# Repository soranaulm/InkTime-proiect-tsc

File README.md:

# InkTime - Open Source Smartwatch

InkTime este un smartwatch open source și accesibil, bazat pe un display e-paper și microcontroller-ul nRF52840.

## Diagramă bloc

```
┌─────────────┐     ┌─────────────────────────────────────────────────┐
│  USB-C      │─5V─▶│                                                 │
└─────────────┘     │                                                 │
                    │  BQ25180YBGR (LiPo Charger)                    │
┌─────────────┐     │         │ VBAT                                  │
│ AKYGA       │────▶│         ▼                                       │
│ LP502030    │     │  RT6160AWSC (DC/DC) ──▶ 3.3V                   │
│ 3.7V 250mAh │     └─────────────────────────────────────────────────┘
└─────────────┘                    │ 3V3
                                   ▼
                    ┌──────────────────────────────┐
                    │         nRF52840              │
                    │      MCU Principal            │
                    │      Bluetooth 5.0            │
                    └──────────────────────────────┘
                         │        │        │        │
                       SPI       I2C     GPIO      SWD
                         │        │        │        │
                    ┌────┘   ┌───┘    ┌───┘    ┌───┘
                    ▼        ▼        ▼        ▼
              e-Paper    ICM42421  FIT0774   Debug
              1.54"      IMU      Vibrații   SWD
              200x200               +
                                  3x Butoane
```

---

## BOM (Bill of Materials)

| Referinta   | Componenta      | Model                  | Cantitate | Link achizitie                                                                  | Datasheet                                                                                                      |
| ----------- | --------------- | ---------------------- | --------- | ------------------------------------------------------------------------------- | -------------------------------------------------------------------------------------------------------------- |
| U1          | MCU             | nRF52840               | 1         | [JLC](https://jlcpcb.com/partdetail/NordicSemiconductor-nRF52840_QIAA/C190794) | [Datasheet](https://4donline.ihs.com/images/VipMasterIC/IC/NRSA/NRSA-S-A0021008244/NRSA-S-A0021008244-1.pdf?hkey=61A2E4C270F0397D049F8F05BD4F1054)  |
| IC1         | LiPo Charger    | BQ25180YBGR            | 1         | [JLC](https://componentsearchengine.com/prices/BQ25180YBGR?manufacturer=Texas%20Instruments)     | [Datasheet](https://www.ti.com/lit/ds/symlink/bq25180.pdf)                                                     |
| IC2         | Haptic Driver   | DRV2605YZFR            | 1         | [JLC](https://componentsearchengine.com/prices/DRV2605YZFR?manufacturer=Texas%20Instruments)     | [Datasheet](https://www.ti.com/lit/ds/symlink/drv2605.pdf)                                                     |
| IC3         | IMU             | BMA423                 | 1         | [JLC](https://componentsearchengine.com/prices/BMA423?manufacturer=BOSCH)                      | [Datasheet](https://4donline.ihs.com/images/VipMasterIC/IC/BSCH/BSCH-S-A0007921771/BSCH-S-A0010021471-1.pdf?hkey=61A2E4C270F0397D049F8F05BD4F1054)    |
| IC9         | DC/DC Converter | RT6160AWSC             | 1         | [JLC](https://componentsearchengine.com/prices/RT6160AWSC?manufacturer=RICHTEK)               | [Datasheet](https://4donline.ihs.com/images/VipMasterIC/IC/RHTK/RHTK-S-A0025617216/RHTK-S-A0025617221-1.pdf?hkey=61A2E4C270F0397D049F8F05BD4F1054)                                |
| U3          | Fuel Gauge      | MAX17048G+T10          | 1         | [JLC](https://componentsearchengine.com/prices/MAX17048G%2BT10?manufacturer=Analog%20Devices)      | [Datasheet](https://4donline.ihs.com/images/VipMasterIC/IC/RHTK/RHTK-S-A0025617216/RHTK-S-A0025617221-1.pdf?hkey=61A2E4C270F0397D049F8F05BD4F1054)         |
| D3          | ESD Protection  | USBLC6-2SC6Y           | 1         | [JLC](https://componentsearchengine.com/prices/USBLC6-2SC6Y?manufacturer=STMicroelectronics)   | [Datasheet](https://www.analog.com/media/en/technical-documentation/data-sheets/MAX17048-MAX17049.pdf?ADICID=SYND_WW_P682800_PF-spglobal)                                             |
| J4          | USB-C Connector | KH-TYPE-C-16P          | 1         | [JLC](https://www.snapeda.com/parts/KH-TYPE-C-16P/kinghelm/view-part/?ref=search&t=KH-TYPE-C-16P&ab_test_case=b)                    | [Datasheet](https://www.snapeda.com/parts/KH-TYPE-C-16P/kinghelm/datasheet/)        |
| J1          | E-Paper Connector | 503480-2400E         | 1         | [JLC](https://componentsearchengine.com/prices/5034802400?manufacturer=Molex)                 | [Datasheet](https://4donline.ihs.com/images/VipMasterIC/IC/MOLE/MOLE-S-A0003522481/MOLE-S-A0010982248-1.pdf?hkey=61A2E4C270F0397D049F8F05BD4F1054)                                      |
| ANT1        | Antena BLE      | 2450AT18B100E          | 1         | [JLC](https://componentsearchengine.com/prices/2450AT18B100E?manufacturer=JOHANSON%20TECHNOLOGY)             | [Datasheet](https://www.johansontechnology.com/docs/1187/2450AT18B100_X8XXogU.pdf)                     |
| X1          | Crystal 32MHz   | SMD 2016               | 1         | [JLC](https://componentsearchengine.com/prices/SMD2016B050TF?manufacturer=Yageo%20Group)                   | [Datasheet](https://4donline.ihs.com/images/VipMasterIC/IC/YAGO/YAGO-S-A0024580626/YAGO-S-A0024591343-1.pdf?hkey=61A2E4C270F0397D049F8F05BD4F1054)                            |
| X2          | Crystal 32.768kHz | SMD 2016             | 1         | [JLC](https://componentsearchengine.com/prices/SMD2016B050TF?manufacturer=Yageo%20Group)               | [Datasheet](https://4donline.ihs.com/images/VipMasterIC/IC/YAGO/YAGO-S-A0024580626/YAGO-S-A0024591343-1.pdf?hkey=61A2E4C270F0397D049F8F05BD4F1054)                               |
| SW1-3       | Buton tactil    | EVP-AKE31A             | 3         | [JLC](https://componentsearchengine.com/prices/EVP-AKE31A?manufacturer=Panasonic)               | [Datasheet](https://industrial.panasonic.com/cdbs/www-data/pdf/ATK0000/ATK0000C434.pdf)                        |
| J2          | SWD Connector   | TC2030-IDC             | 1         | [JLC](https://componentsearchengine.com/prices/TC2030-IDC?manufacturer=Tag%20Connect)             | [Datasheet](https://4donline.ihs.com/images/VipMasterIC/IC/TGCN/TGCN-S-A0008988129/TGCN-S-A0008988129-1.pdf?hkey=61A2E4C270F0397D049F8F05BD4F1054)                   |
| Q2          | MOSFET P-ch     | DMG2305UX-7            | 1         | [JLC](https://componentsearchengine.com/prices/DMG2305UX-7?manufacturer=Diodes%20Incorporated)                 | [Datasheet](https://4donline.ihs.com/images/VipMasterIC/IC/DIOD/DIOD-S-A0013043571/DIOD-S-A0013120650-1.pdf?hkey=61A2E4C270F0397D049F8F05BD4F1054)                                            |
| Q3          | MOSFET N-ch     | SI1308EDL-T1-GE3       | 1         | [JLC](https://componentsearchengine.com/prices/Si1308EDL-T1-GE3?manufacturer=Vishay)             | [Datasheet](https://4donline.ihs.com/images/VipMasterIC/IC/VISH/VISH-S-A0000692786/VISH-S-A0000692786-1.pdf?hkey=61A2E4C270F0397D049F8F05BD4F1054)                                                   |
| D2, D4, D5  | Dioda Schottky  | MBR0530                | 3         | [JLC](https://componentsearchengine.com/prices/MBR0530?manufacturer=MCC)           | [Datasheet](https://4donline.ihs.com/images/VipMasterIC/IC/MCCC/MCCCS04194/MCCCS04194-1.pdf?hkey=61A2E4C270F0397D049F8F05BD4F1054)                                         |
| L1          | Inductanta 0.47µH | FTC252012SR47MBCA    | 1         | [JLC](https://jlcpcb.com/partdetail/6763488-FTC252012SR47MBCA/C5832368)                 |
| L2          | Inductanta 15nH | RF matching 0201       | 1         | [JLC](https://jlcpcb.com/partdetail/Sunlord-SDCL0201C15NJTDF/C389547)          |     -                   |
| L3          | Inductanta 3.9nH | RF matching 0201      | 1         | [JLC](https://jlcpcb.com/partdetail/Sunlord-SDCL0201C3N9STDF/C389544)          |     -                   |
| L5          | Inductanta 68µH | EPD driver SMD         | 1         | [JLC](https://jlcpcb.com/partdetail/Sumida-CDMC4D28NP680MC/C408336)            |     -                       |
| L7          | Inductanta 10µH | DC/DC SMD              | 1         | [JLC](https://jlcpcb.com/partdetail/Sunlord-MWSA0402S100MT/C408352)            |     -                     |
| C*          | Condensatoare   | 100nF decuplare 0201   | multiple  | [JLC](https://jlcpcb.com/partdetail/Samsung-CL03B104KO3NNNC/C15195)            | -                                                                                                               |
| C*          | Condensatoare   | >100nF bulk 0402       | multiple  | [JLC](https://jlcpcb.com/partdetail/Samsung-CL05A475KP5NRNC/C25771)            | -                                                                                                               |
| R*          | Rezistente      | Diverse valori 0201    | multiple  | [JLC](https://jlcpcb.com/partdetail/UNI-ROYAL-0201WAF1001T5E/C17513)           | -                                                                                                               |

---

## Descriere funcționalitate hardware

### MCU — nRF52840

Microcontroller-ul principal al proiectului. Are integrat Bluetooth 5.0, suportă SPI, I2C, UART și GPIO. Rulează la 3.3V, consumă ~1.5mA activ și sub 2μA în deep sleep. Procesor ARM Cortex-M4F la 64MHz, 1MB Flash și 256KB RAM.

### Display e-Paper 1.54" (Waveshare V2)

Display electrofotoreic bistabil cu rezoluție 200×200 pixeli. Conectat prin SPI 4 fire. Consumul în deep sleep este sub 2μA. Imaginea rămâne afișată fără consum de energie (bi-stable) — ideal pentru smartwatch.

### Baterie AKYGA LP502030

Baterie Li-Po de 250mAh, 3.7V nominal. Se conectează direct la două test pad-uri de pe PCB (TP_BAT și TP_BAT_GND), fără conector JST, pentru economisirea spațiului în carcasă.

### LiPo Charger — BQ25180YBGR

Circuit de încărcare a bateriei Li-Po, conectat prin I2C la MCU. Suportă încărcare CC/CV, protecție la supraîncărcare (4.3V) și supradescărcare (2.5V). Tensiunea de intrare vine de la USB-C (VBUS 5V).

### DC/DC Converter — RT6160AWSC

Convertor buck care generează 3.3V pentru MCU și restul componentelor. Eficiență ~90%, comunicație I2C pentru configurare dinamică a tensiunii de ieșire.

### IMU — BMA423

Accelerometru 3-axis conectat prin I2C. Detectează mișcări, orientare, pași și gesture-uri. Întreruperile IMU_INT1 și IMU_INT2 sunt conectate la GPIO-uri ale MCU.

### Haptic Driver — DRV2605YZFR

Driver pentru motorul de vibrații, conectat prin I2C. Controlează FIT0774 și permite pattern-uri de vibrații complexe pentru notificări tactile diferențiate.

### Motor vibrații — FIT0774

Motor DC de vibrații (10×2.7mm), controlat prin DRV2605 via tranzistor N-channel. Folosit pentru notificări tactile.

### Fuel Gauge — MAX17048G+T10

Monitorizare nivel baterie prin I2C. Oferă MCU-ului informații despre starea de încărcare (SOC) a bateriei.

### ESD Protection — USBLC6-2SC6Y

Protecție ESD pe liniile USB-C (VBUS, D+, D-) pentru protejarea MCU-ului.

### Butoane

3 butoane tactile SMD (SW_UP, SW_ENT, SW_DN) cu condensatoare de debounce, conectate la GPIO-urile MCU.

---

## Pini nRF52840 utilizați

| Componentă         | Semnal     | Pin nRF52840 | Interfață | Motiv                     |
| ------------------ | ---------- | ------------ | --------- | ------------------------- |
| e-Paper            | EPD_CS     | P0.04        | SPI       | Chip Select display       |
| e-Paper            | EPD_BUSY   | P0.13        | GPIO      | Status display            |
| e-Paper            | EPD_RST    | P0.14        | GPIO      | Reset display             |
| e-Paper            | MOSI       | P0.30        | SPI       | Date SPI                  |
| e-Paper            | SCK        | P0.29        | SPI       | Clock SPI                 |
| I2C (toți)         | SDA        | P0.06        | I2C       | Date I2C shared bus       |
| I2C (toți)         | SCL        | P0.07        | I2C       | Clock I2C shared bus      |
| IMU                | IMU_INT1   | P0.08        | GPIO      | Întrerupere IMU primară   |
| IMU                | IMU_INT2   | P0.09        | GPIO      | Întrerupere IMU secundară |
| LiPo Charger       | PMIC_INT   | P0.11        | GPIO      | Întrerupere PMIC/charger  |
| Haptic Driver      | HAPTIC_EN  | P0.12        | GPIO      | Enable motor vibrații     |
| SWD                | SWDIO      | P1.02        | SWD       | Debug data                |
| SWD                | SWDCLK     | P1.00        | SWD       | Debug clock               |

---

## Calcul consum de energie

| Componentă        | Consum activ      | Consum sleep |
| ----------------- | ----------------- | ------------ |
| nRF52840          | ~1.5mA            | ~2μA         |
| e-Paper display   | ~8mAs/refresh     | ~2μA         |
| BMA423 IMU        | ~0.5mA            | ~6μA         |
| BQ25180 Charger   | ~50mA (încărcare) | ~5μA         |
| RT6160 DC/DC      | eficiență ~90%    | -            |
| DRV2605 + FIT0774 | ~50mA (vibrație)  | ~0μA         |

**Estimare autonomie:**

- Baterie: 250mAh
- Consum mediu estimat (refresh 1x/min, BT off, fără vibrații): ~0.5mA
- Autonomie estimată: **~500 ore (~20 zile)**

## Arhitectura PCB
PCB-ul a fost realizat pe 4 straturi, cu următoarea structură:
StratRolLayer 1 (TOP)Semnale + componenteLayer 2 (c63Route63)Plan de masă GNDLayer 3Semnale interneLayer 4 (BOTTOM)Semnale + plan de masă
Rutarea pe 4 straturi a permis o densitate mai mare de trasee și o mai bună integritate a semnalului, în special pentru traseele RF.
Via stitching a fost aplicat între planurile de masă TOP și BOTTOM, în special în jurul circuitului radio (nRF52840 + antenă 2450AT18B100E).
Zona de sub antenă a fost decupată — nu există plan de masă și nu sunt rutate semnale sub antenă, conform cerințelor pentru performanță RF optimă.

## Decizii de design

Bateria se conectează direct la test pad-urile TP_BAT și TP_BAT_GND (fără conector JST) pentru economisirea spațiului.
PCB grosime 1mm (nu 1.6mm standard) pentru a încăpea în carcasă.
Antena plasată spre exteriorul PCB-ului, cu decupaj sub ea.
Toate componentele plasate exclusiv pe layer-ul TOP.
Condensatoare de decuplare 100nF (0201) cât mai aproape de pinii de alimentare.
Trasee de putere rutate cu 0.3mm, semnale de date cu minim 0.15mm.
Trasee fără unghiuri drepte.

## Erori DRC acceptate
Am acceptat erori de tip: 
- Smd-Via, aparute in urma via in pad;
- Cele de tip Wire-Wire, care sunt doar in pad, nu pe trasee si le-am dat approve caci, real-life, putem potrivi acele fire in pad astfel incat sa nu se suprapuna;
- Cele de tip Wire-Via, Smd-Wire cu aceeasi mentiune;
- Cele de tip Solid-Polygon Shape-Pad, aparute in urma plasarii butoanelor pe PCB, care nu reprezinta o problema(ignorate conform cerintelor proiectului;

## Imagini

## Licență

Apache 2.0 — vezi fișierul [LICENSE](LICENSE)

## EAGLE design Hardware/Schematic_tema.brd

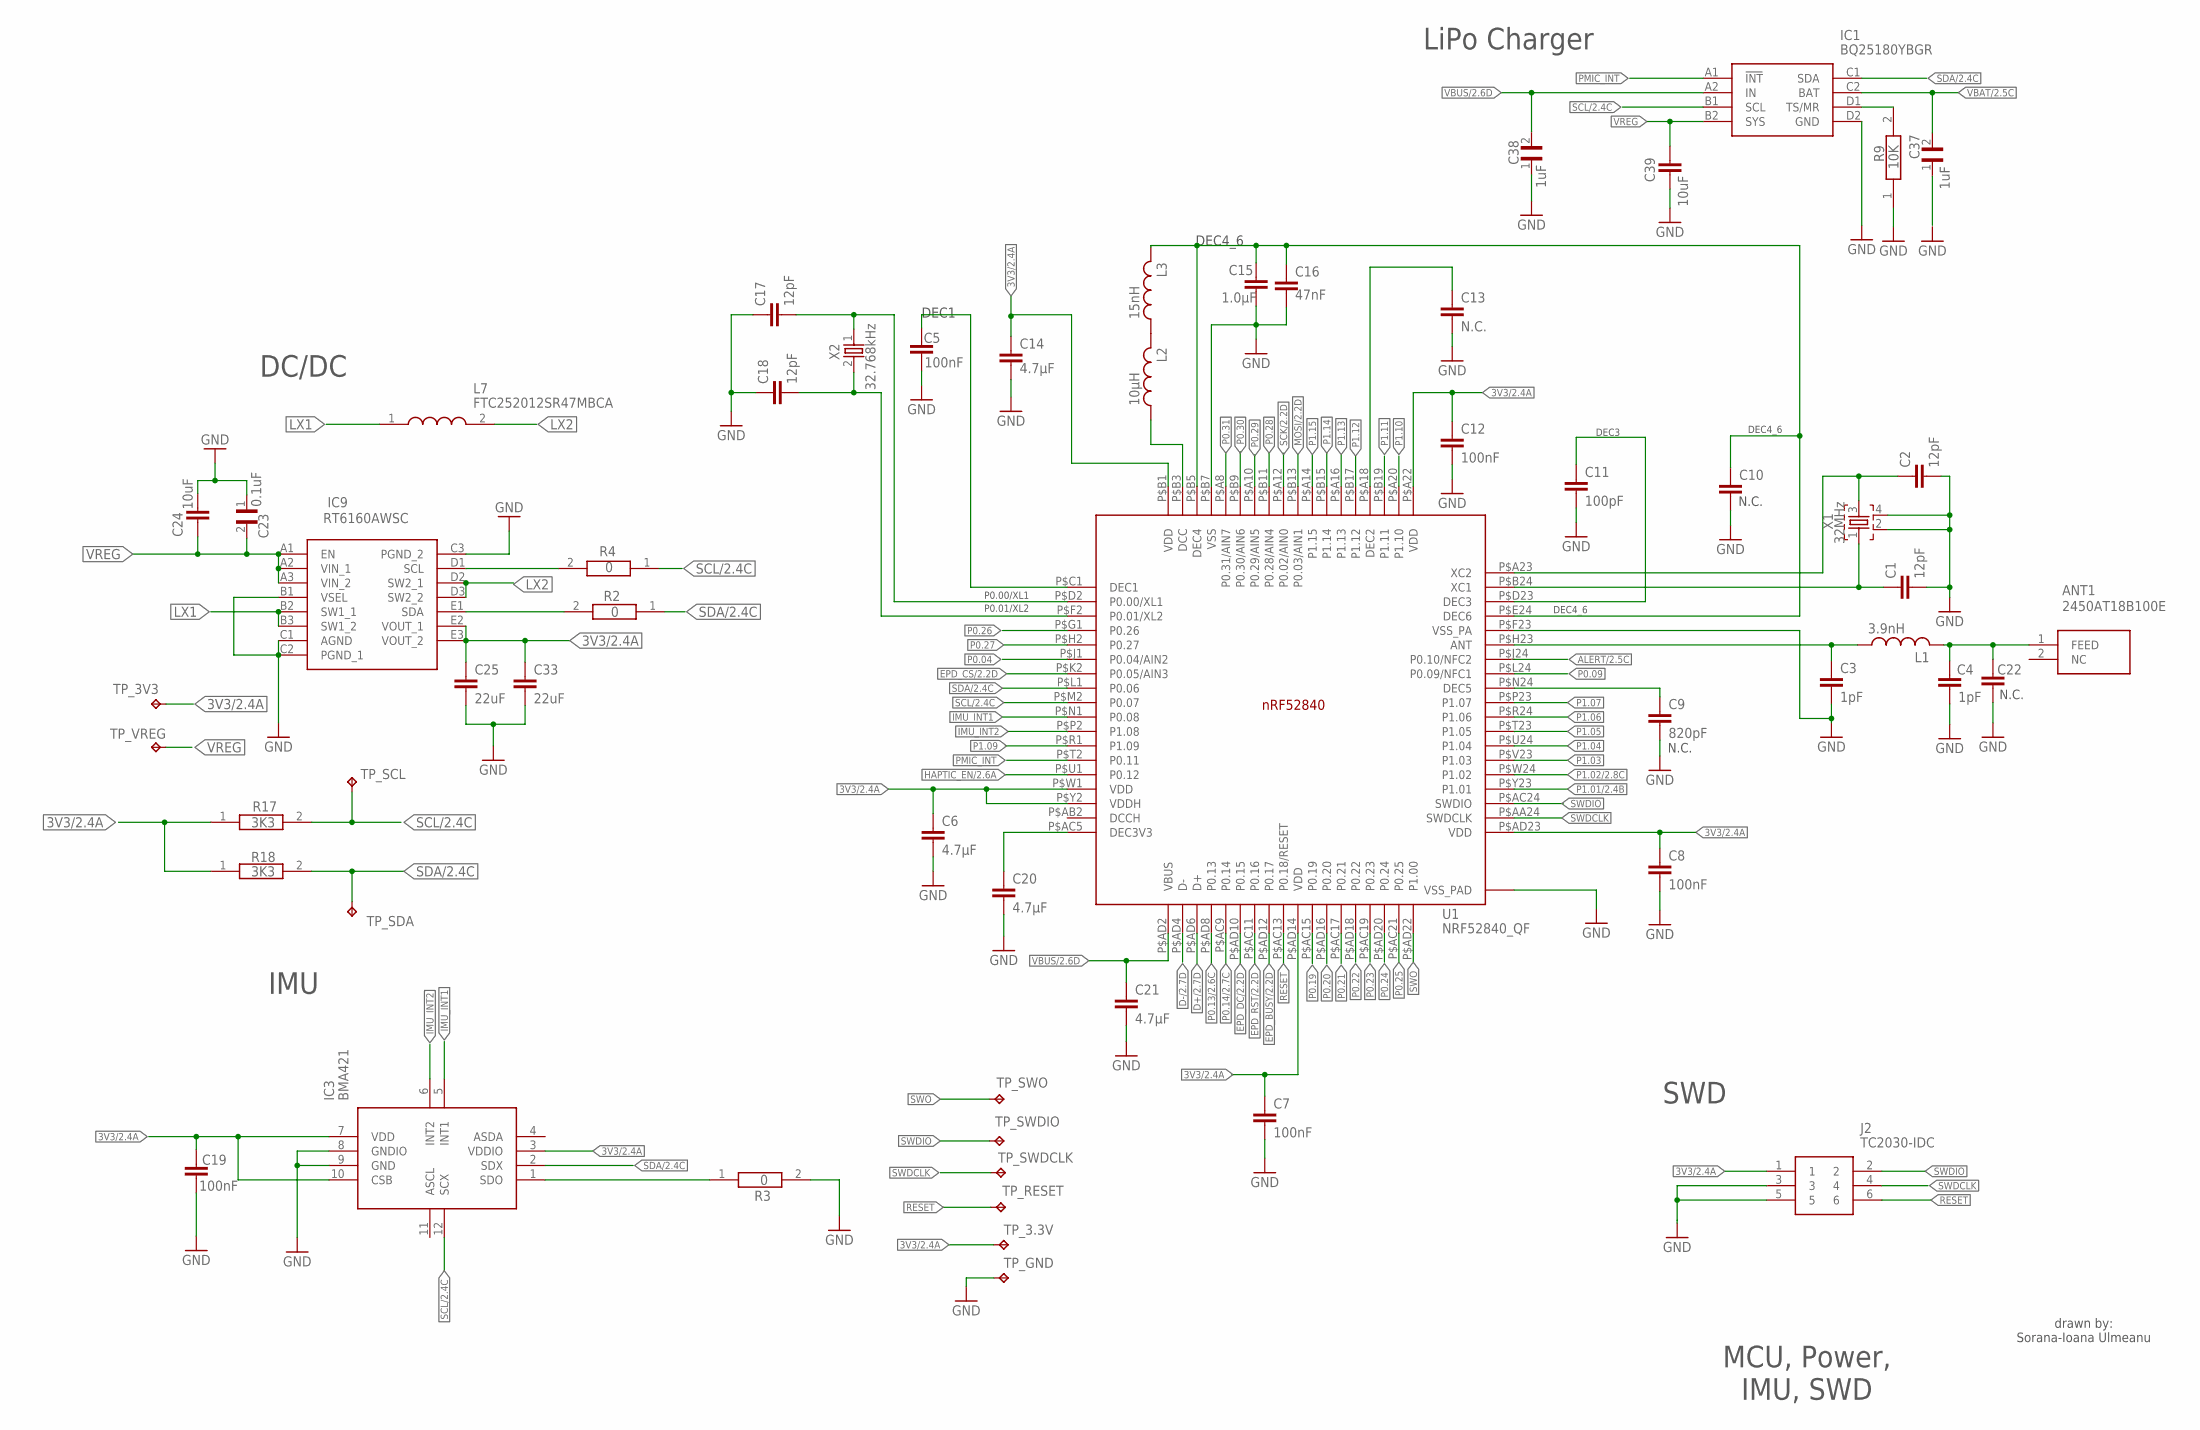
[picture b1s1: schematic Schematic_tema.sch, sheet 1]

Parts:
ANT1: 2450AT18B100E; 2450AT18B100E_ANTC3216X140N
C1, C2, C17, C18: 12pF; PERFECT_0402_0402
C3, C4: 1pF; PERFECT_0402_0402
C5, C7, C8, C12, C19: 100nF; PERFECT_0402_0402
C6, C14, C20, C21: 4.7µF; PERFECT_0402_0402
C9: 820pF; PERFECT_0402_0402
C10, C22: PERFECT_0402_CAP_0402; PERFECT_0402_0402
C11: 100pF; PERFECT_0402_0402
C13: N.C.; PERFECT_0402_0402
C15: 1.0µF; PERFECT_0402_0402
C16: 47nF; PERFECT_0402_0402
C23: 0.1uF; GRM011R60J152KE01L_1_0201
C24, C39: 10uF; PERFECT_0402_0402
C25, C33: 22uF; PERFECT_0402_0402
C37, C38: 1uF; GRM011R60J152KE01L_1_0201
IC1: BQ25180YBGR; BQ25180YBGR_BGA8C40P2X4_100X155X50
IC3: BMA421; BMA423_BMA423
IC9: RT6160AWSC; RT6160AWSC_BGA15C40P3X5_140X230X60
J2: TC2030-IDC; TC2030-IDC_TC2030IDC
L1: 3.9nH; NORDIC_NRF_2_RESC0402_L
L2: 10µH; NORDIC_NRF_2_RESC0402_L
L3: 15nH; NORDIC_NRF_2_RESC0402_L
L7: FTC252012SR47MBCA; MLP2016SR47MT0S1_INDC2016X100N
R2, R4: 0; CPF0201D7K68C1_0201
R3: 0; ERA-1AEB3401C_0201
R9: 10K; CPF0201D7K68C1_0201
R17, R18: 3K3; CPF0201D7K68C1_0201
TP_3.3V, TP_3V3: HECTOR_WATCH_1_TPTP20R; HECTOR_WATCH_1_TP20R
TP_GND: HECTOR_WATCH_1_TPTP20R; HECTOR_WATCH_1_TP20R
TP_RESET: HECTOR_WATCH_1_TPTP20R; HECTOR_WATCH_1_TP20R
TP_SCL: HECTOR_WATCH_1_TPTP20R; HECTOR_WATCH_1_TP20R
TP_SDA: HECTOR_WATCH_1_TPTP20R; HECTOR_WATCH_1_TP20R
TP_SWDCLK: HECTOR_WATCH_1_TPTP20R; HECTOR_WATCH_1_TP20R
TP_SWDIO: HECTOR_WATCH_1_TPTP20R; HECTOR_WATCH_1_TP20R
TP_SWO: HECTOR_WATCH_1_TPTP20R; HECTOR_WATCH_1_TP20R
TP_VREG: HECTOR_WATCH_1_TPTP20R; HECTOR_WATCH_1_TP20R
U1: NRF52840_QF; NORDIC_NRF_4_AQFN50P700X700X85_HS-74N
X1: 32MHz; NORDIC_NRF_BT-XTAL_2016_N
X2: 32.768kHz; NORDIC_NRF_1_XTAL_3215_N

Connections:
3V3/2.4A: C6.1, C7.1, C8.1, C12.1, C14.1, C19.1, C25.1, C33.1, IC3.3 (VDDIO), IC3.7 (VDD), IC3.10 (CSB), IC9.E2 (VOUT_1), IC9.E3 (VOUT_2), J2.1, R17.1, R18.1, TP_3.3V.TP, TP_3V3.TP, U1.P$A22 (VDD), U1.P$AD14 (VDD), U1.P$AD23 (VDD), U1.P$B1 (VDD), U1.P$W1 (VDD), U1.P$Y2 (VDDH)
ALERT/2.5C: U1.P$J24 (P0.10/NFC2)
D+/2.7D: U1.P$AD6 (D+)
D-/2.7D: U1.P$AD4 (D-)
EPD_BUSY/2.2D: U1.P$AD12 (P0.17)
EPD_CS/2.2D: U1.P$K2 (P0.05/AIN3)
EPD_DC/2.2D: U1.P$AD10 (P0.15)
EPD_RST/2.2D: U1.P$AC11 (P0.16)
GND: C1.2, C2.2, C3.2, C4.2, C5.1, C6.2, C7.2, C8.2, C9.2, C10.2, C11.2, C12.2, C13.2, C14.2, C15.2, C16.2, C17.1, C18.1, C19.2, C20.2, C21.2, C22.2, C23.1, C24.1, C25.2, C33.2, C38.1, C39.2, IC1.D2 (GND), IC3.8 (GNDIO), IC3.9 (GND), IC9.B1 (VSEL), IC9.C1 (AGND), IC9.C2 (PGND_1), IC9.C3 (PGND_2), J2.3, J2.5, R3.2, R9.1, TP_GND.TP, U1.P$74 (VSS_PAD), U1.P$75 (VSS_PAD), U1.P$76 (VSS_PAD), U1.P$77 (VSS_PAD), U1.P$78 (VSS_PAD), U1.P$79 (VSS_PAD), U1.P$80 (VSS_PAD), U1.P$81 (VSS_PAD), U1.P$82 (VSS_PAD), U1.P$83 (VSS_PAD), U1.P$84 (VSS_PAD), U1.P$85 (VSS_PAD), U1.P$86 (VSS_PAD), U1.P$87 (VSS_PAD), U1.P$88 (VSS_PAD), U1.P$89 (VSS_PAD), U1.P$90 (VSS_PAD), U1.P$B7 (VSS), U1.P$F23 (VSS_PA), X1.2, X1.4; also elsewhere on the board
HAPTIC_EN/2.6A: U1.P$U1 (P0.12)
IMU_INT1: IC3.5 (INT1), U1.P$N1 (P0.08)
IMU_INT2: IC3.6 (INT2), U1.P$P2 (P1.08)
LX1: IC9.B2 (SW1_1), IC9.B3 (SW1_2), L7.1
LX2: IC9.D2 (SW2_1), IC9.D3 (SW2_2), L7.2
MOSI/2.2D: U1.P$B13 (P0.03/AIN1)
unnamed: IC3.1 (SDO), R3.1
unnamed: C5.2, U1.P$C1 (DEC1)
unnamed: L2.2, U1.P$B3 (DCC)
unnamed: IC9.D1 (SCL), R4.2
unnamed: C10.1, C15.1, C16.1, L3.1, U1.P$B5 (DEC4), U1.P$E24 (DEC6)
unnamed: IC1.D1 (TS/MR), R9.2
unnamed: IC9.E1 (SDA), R2.2
unnamed: C13.1, U1.P$A18 (DEC2)
unnamed: L2.1, L3.2
unnamed: C17.2, U1.P$D2 (P0.00/XL1), X2.1
unnamed: C18.2, U1.P$F2 (P0.01/XL2), X2.2
unnamed: C20.1, U1.P$AC5 (DEC3V3)
unnamed: C11.1, U1.P$D23 (DEC3)
unnamed: C2.1, U1.P$A23 (XC2), X1.3
unnamed: C1.1, U1.P$B24 (XC1), X1.1
unnamed: C3.1, L1.1, U1.P$H23 (ANT)
unnamed: ANT1.1 (FEED), C4.1, C22.1, L1.2
unnamed: C9.1, U1.P$N24 (DEC5)
P0.04: U1.P$J1 (P0.04/AIN2)
P0.09: U1.P$L24 (P0.09/NFC1)
P0.13/2.6C: U1.P$AD8 (P0.13)
P0.14/2.7C: U1.P$AC9 (P0.14)
P0.19: U1.P$AC15 (P0.19)
P0.20: U1.P$AD16 (P0.20)
P0.21: U1.P$AC17 (P0.21)
P0.22: U1.P$AD18 (P0.22)
P0.23: U1.P$AC19 (P0.23)
P0.24: U1.P$AD20 (P0.24)
P0.25: U1.P$AC21 (P0.25)
P0.26: U1.P$G1 (P0.26)
P0.27: U1.P$H2 (P0.27)
P0.28: U1.P$B11 (P0.28/AIN4)
P0.29: U1.P$A10 (P0.29/AIN5)
P0.30: U1.P$B9 (P0.30/AIN6)
P0.31: U1.P$A8 (P0.31/AIN7)
P1.01/2.4B: U1.P$Y23 (P1.01)
P1.02/2.8C: U1.P$W24 (P1.02)
P1.03: U1.P$V23 (P1.03)
P1.04: U1.P$U24 (P1.04)
P1.05: U1.P$T23 (P1.05)
P1.06: U1.P$R24 (P1.06)
P1.07: U1.P$P23 (P1.07)
P1.09: U1.P$R1 (P1.09)
P1.10: U1.P$A20 (P1.10)
P1.11: U1.P$B19 (P1.11)
P1.12: U1.P$B17 (P1.12)
P1.13: U1.P$A16 (P1.13)
P1.14: U1.P$B15 (P1.14)
P1.15: U1.P$A14 (P1.15)
PMIC_INT: IC1.A1 (!INT), U1.P$T2 (P0.11)
RESET: J2.6, TP_RESET.TP, U1.P$AC13 (P0.18/RESET)
SCK/2.2D: U1.P$A12 (P0.02/AIN0)
SCL/2.4C: IC1.B1 (SCL), IC3.12 (SCX), R4.1, R17.2, TP_SCL.TP, U1.P$M2 (P0.07)
SDA/2.4C: IC1.C1 (SDA), IC3.2 (SDX), R2.1, R18.2, TP_SDA.TP, U1.P$L1 (P0.06)
SWDCLK: J2.4, TP_SWDCLK.TP, U1.P$AA24 (SWDCLK)
SWDIO: J2.2, TP_SWDIO.TP, U1.P$AC24 (SWDIO)
SWO: TP_SWO.TP, U1.P$AD22 (P1.00)
VBAT/2.5C: C37.2, IC1.C2 (BAT)
VBUS/2.6D: C21.1, C38.2, IC1.A2 (IN), U1.P$AD2 (VBUS)
VREG: C23.2, C24.2, C39.1, IC1.B2 (SYS), IC9.A1 (EN), IC9.A2 (VIN_1), IC9.A3 (VIN_2), TP_VREG.TP

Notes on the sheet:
DC/DC
IMU
SWD
LiPo Charger
P0.00/XL1
P0.01/XL2
DEC4_6
DEC3
N.C.
MCU, Power, IMU, SWD
drawn by: Sorana-Ioana Ulmeanu
DEC1

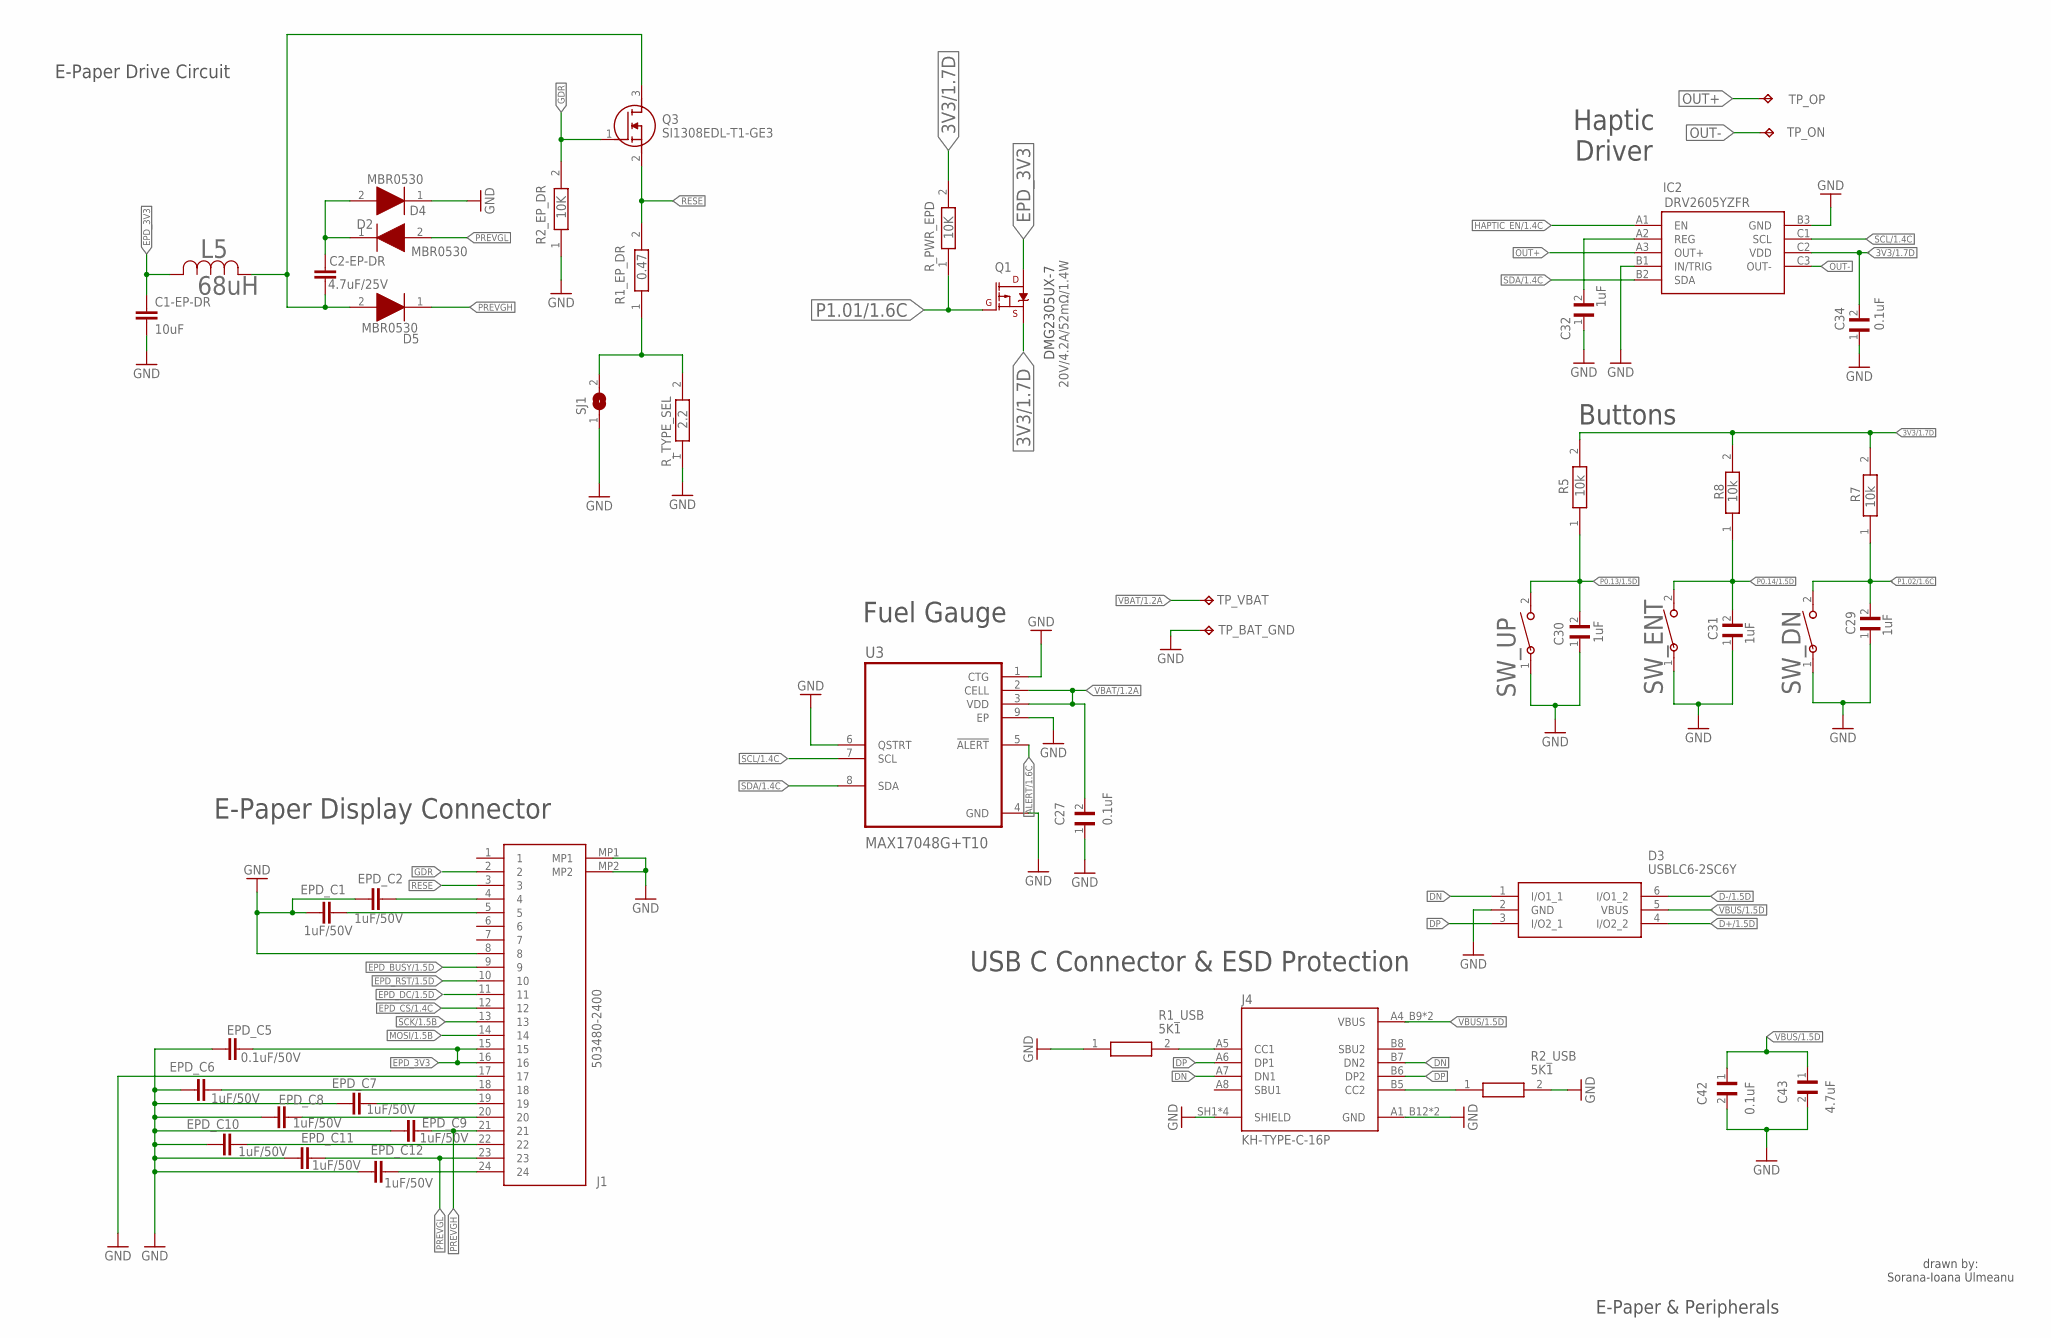
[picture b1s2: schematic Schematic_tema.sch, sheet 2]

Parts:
C1-EP-DR: 10uF; PERFECT_0402_0402
C2-EP-DR: 4.7uF/25V; PERFECT_0402_0402
C27, C42: 0.1uF; GRM011R60J152KE01L_1_0201
C29, C30, C31: 1uF; GRM011R60J152KE01L_1_0201
C32: 1uF; GRM011R60J152KE01L_2_CAPC0201X13N
C34: 0.1uF; GRM011R60J152KE01L_2_CAPC0201X13N
C43: 4.7uF; GRM011R60J152KE01L_1_0201
D2, D4, D5: MBR0530; ESP32_C6_LIBRARY_5_SOD3716X135N
D3: USBLC6-2SC6Y; ESP32_C6_LIBRARY_3_SOT95P280X145-6N
EPD_C1, EPD_C2, EPD_C6, EPD_C7, EPD_C8, EPD_C9, EPD_C10, EPD_C11, EPD_C12: 1uF/50V; PERFECT_0402_0402
EPD_C5: 0.1uF/50V; PERFECT_0402_0402
IC2: DRV2605YZFR; DRV2605YZFR_BGA9C50P3X3_144X144X62
J1: 503480-2400; 503480-2400_5034802400
J4: KH-TYPE-C-16P; KH-TYPE-C-16P_KINGHELM_KH-TYPE-C-16P
L5: 68uH; ESP32_C6_LIBRARY_2_IND_4828-WE-TPC_WRE
Q1: 20V/4.2A/52mΩ/1.4W; ESP32_C6_LIBRARY_4_ESP32_C6_LIBRARY_4_ESP32_C6_LIBRARY_4_ES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
Q3: SI1308EDL-T1-GE3; ESP32_C6_LIBRARY_6_SOT65P210X110-3N
R1_EP_DR: 0.47; CPF0201D7K68C1_0201
R1_USB, R2_USB: 5K1; CPF0201D7K68C1_0201
R2_EP_DR: 10K; ERA-1AEB3401C_0201
R5, R7, R8: 10k; CPF0201D7K68C1_0201
R_PWR_EPD: 10K; CPF0201D7K68C1_0201
R_TYPE_SEL: 2.2; ERA-1AEB3401C_0201
SJ1: ESP32_C6_LIBRARY_7_JUMPER_SJ
SW_DN: 2025-10-22_07-23-44_LIBRARY_EVP-AKE31ASW_EVP-AKE3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; 2025-10-22_07-23-44_LIBRARY_SW_EVP-AKE31A_PAN
SW_ENT: 2025-10-22_07-23-44_LIBRARY_EVP-AKE31ASW_EVP-AKE3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; 2025-10-22_07-23-44_LIBRARY_SW_EVP-AKE31A_PAN
SW_UP: 2025-10-22_07-23-44_LIBRARY_EVP-AKE31ASW_EVP-AKE3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; 2025-10-22_07-23-44_LIBRARY_SW_EVP-AKE31A_PAN
TP_BAT_GND: HECTOR_WATCH_1_TPTP20R; HECTOR_WATCH_1_TP20R
TP_ON: HECTOR_WATCH_1_TPTP20R; HECTOR_WATCH_1_TP20R
TP_OP: HECTOR_WATCH_1_TPTP20R; HECTOR_WATCH_1_TP20R
TP_VBAT: HECTOR_WATCH_1_TPTP20R; HECTOR_WATCH_1_TP20R
U3: MAX17048G+T10; ESP32_C6_LIBRARY_SON50P200X200X80-9N

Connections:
3V3/1.7D: C34.2, IC2.C2 (VDD), Q1.2 (S), R5.2, R7.2, R8.2, R_PWR_EPD.2
ALERT/1.6C: U3.5 (!ALERT)
D+/1.5D: D3.4 (I/O2_2)
D-/1.5D: D3.6 (I/O1_2)
DN: D3.1 (I/O1_1), J4.A7 (DN1), J4.B7 (DN2)
DP: D3.3 (I/O2_1), J4.A6 (DP1), J4.B6 (DP2)
EPD_3V3: C1-EP-DR.1, EPD_C5.2, J1.15, J1.16, L5.2, Q1.3 (D)
EPD_BUSY/1.5D: J1.9
EPD_CS/1.4C: J1.12
EPD_DC/1.5D: J1.11
EPD_RST/1.5D: J1.10
GDR: J1.2, Q3.1 (G), R2_EP_DR.2
GND: C1-EP-DR.2, C27.1, C29.1, C30.1, C31.1, C32.1, C34.1, C42.2, C43.2, D3.2 (GND), D4.1 (K), EPD_C1.1, EPD_C2.1, EPD_C5.1, EPD_C6.1, EPD_C7.1, EPD_C8.1, EPD_C9.1, EPD_C10.1, EPD_C11.1, EPD_C12.1, IC2.B1 (IN/TRIG), IC2.B3 (GND), J1.8, J1.17, J1.MP1, J1.MP2, J4.A1_B12 (GND), J4.A12_B1 (GND), J4.SH1 (SHIELD), J4.SH2 (SHIELD), J4.SH3 (SHIELD), J4.SH4 (SHIELD), R1_USB.1, R2_EP_DR.1, R2_USB.2, R_TYPE_SEL.1, SJ1.1, SW_DN.1, SW_ENT.1, SW_UP.1, TP_BAT_GND.TP, U3.1 (CTG), U3.4 (GND), U3.6 (QSTRT), U3.9 (EP); also elsewhere on the board
HAPTIC_EN/1.4C: IC2.A1 (EN)
MOSI/1.5B: J1.14
unnamed: C2-EP-DR.2, D5.2 (A), L5.1, Q3.3 (D)
unnamed: R1_EP_DR.1, R_TYPE_SEL.2, SJ1.2
unnamed: C2-EP-DR.1, D2.1 (K), D4.2 (A)
unnamed: EPD_C2.2, J1.4
unnamed: C32.2, IC2.A2 (REG)
unnamed: EPD_C1.2, J1.5
unnamed: J4.A5 (CC1), R1_USB.2
unnamed: EPD_C6.2, J1.18
unnamed: EPD_C7.2, J1.19
unnamed: EPD_C8.2, J1.20
unnamed: J4.B5 (CC2), R2_USB.1
unnamed: EPD_C10.2, J1.22
unnamed: EPD_C12.2, J1.24
OUT+: IC2.A3 (OUT+), TP_OP.TP
OUT-: IC2.C3 (OUT-), TP_ON.TP
P0.13/1.5D: C30.2, R5.1, SW_UP.2
P0.14/1.5D: C31.2, R8.1, SW_ENT.2
P1.01/1.6C: Q1.1 (G), R_PWR_EPD.1
P1.02/1.6C: C29.2, R7.1, SW_DN.2
PREVGH: D5.1 (K), EPD_C9.2, J1.21
PREVGL: D2.2 (A), EPD_C11.2, J1.23
RESE: J1.3, Q3.2 (S), R1_EP_DR.2
SCK/1.5B: J1.13
SCL/1.4C: IC2.C1 (SCL), U3.7 (SCL)
SDA/1.4C: IC2.B2 (SDA), U3.8 (SDA)
VBAT/1.2A: C27.2, TP_VBAT.TP, U3.2 (CELL), U3.3 (VDD)
VBUS/1.5D: C42.1, C43.1, D3.5 (VBUS), J4.A4_B9 (VBUS), J4.A9_B4 (VBUS)

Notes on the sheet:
E-Paper Drive Circuit
DMG2305UX-7
Haptic Driver
Buttons
Fuel Gauge
E-Paper Display Connector
USB C Connector & ESD Protection
E-Paper & Peripherals
drawn by: Sorana-Ioana Ulmeanu

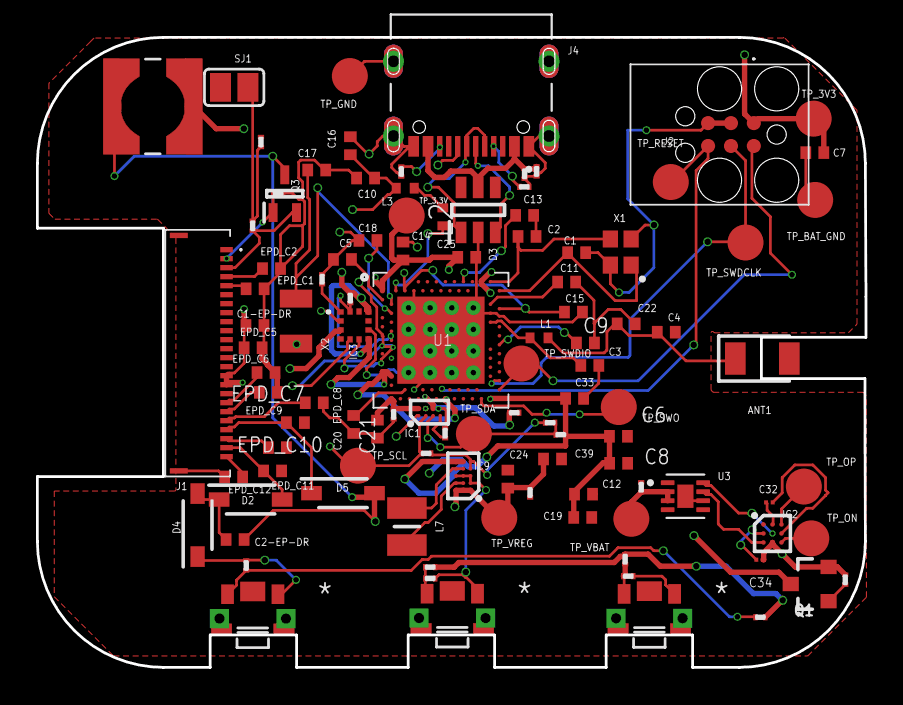
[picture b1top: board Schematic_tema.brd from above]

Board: 4 copper layers, 46.0 x 35.0 mm, 105 parts (0 on the bottom side), 65 nets.

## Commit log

2026-04-09 Need to add gerbers and images
2026-04-10 Add all project files
2026-04-10 Add complete README
2026-04-10 Forgot about the diagram; Need to refine the entire project later
2026-04-17 Readme
2026-04-17 Done with the datasheets
2026-04-17 Updated links
2026-04-17 Finally I hope
2026-04-21 Updated the entire project
2026-04-21 Done
2026-04-21 Done with the images
2026-04-22 Final version

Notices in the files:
parts and their libraries:
COPYRIGHT: Copyright (C) 2024 Ultra Librarian. All rights reserved.
COPYRIGHT: Copyright (C) 2025 Ultra Librarian. All rights reserved.
